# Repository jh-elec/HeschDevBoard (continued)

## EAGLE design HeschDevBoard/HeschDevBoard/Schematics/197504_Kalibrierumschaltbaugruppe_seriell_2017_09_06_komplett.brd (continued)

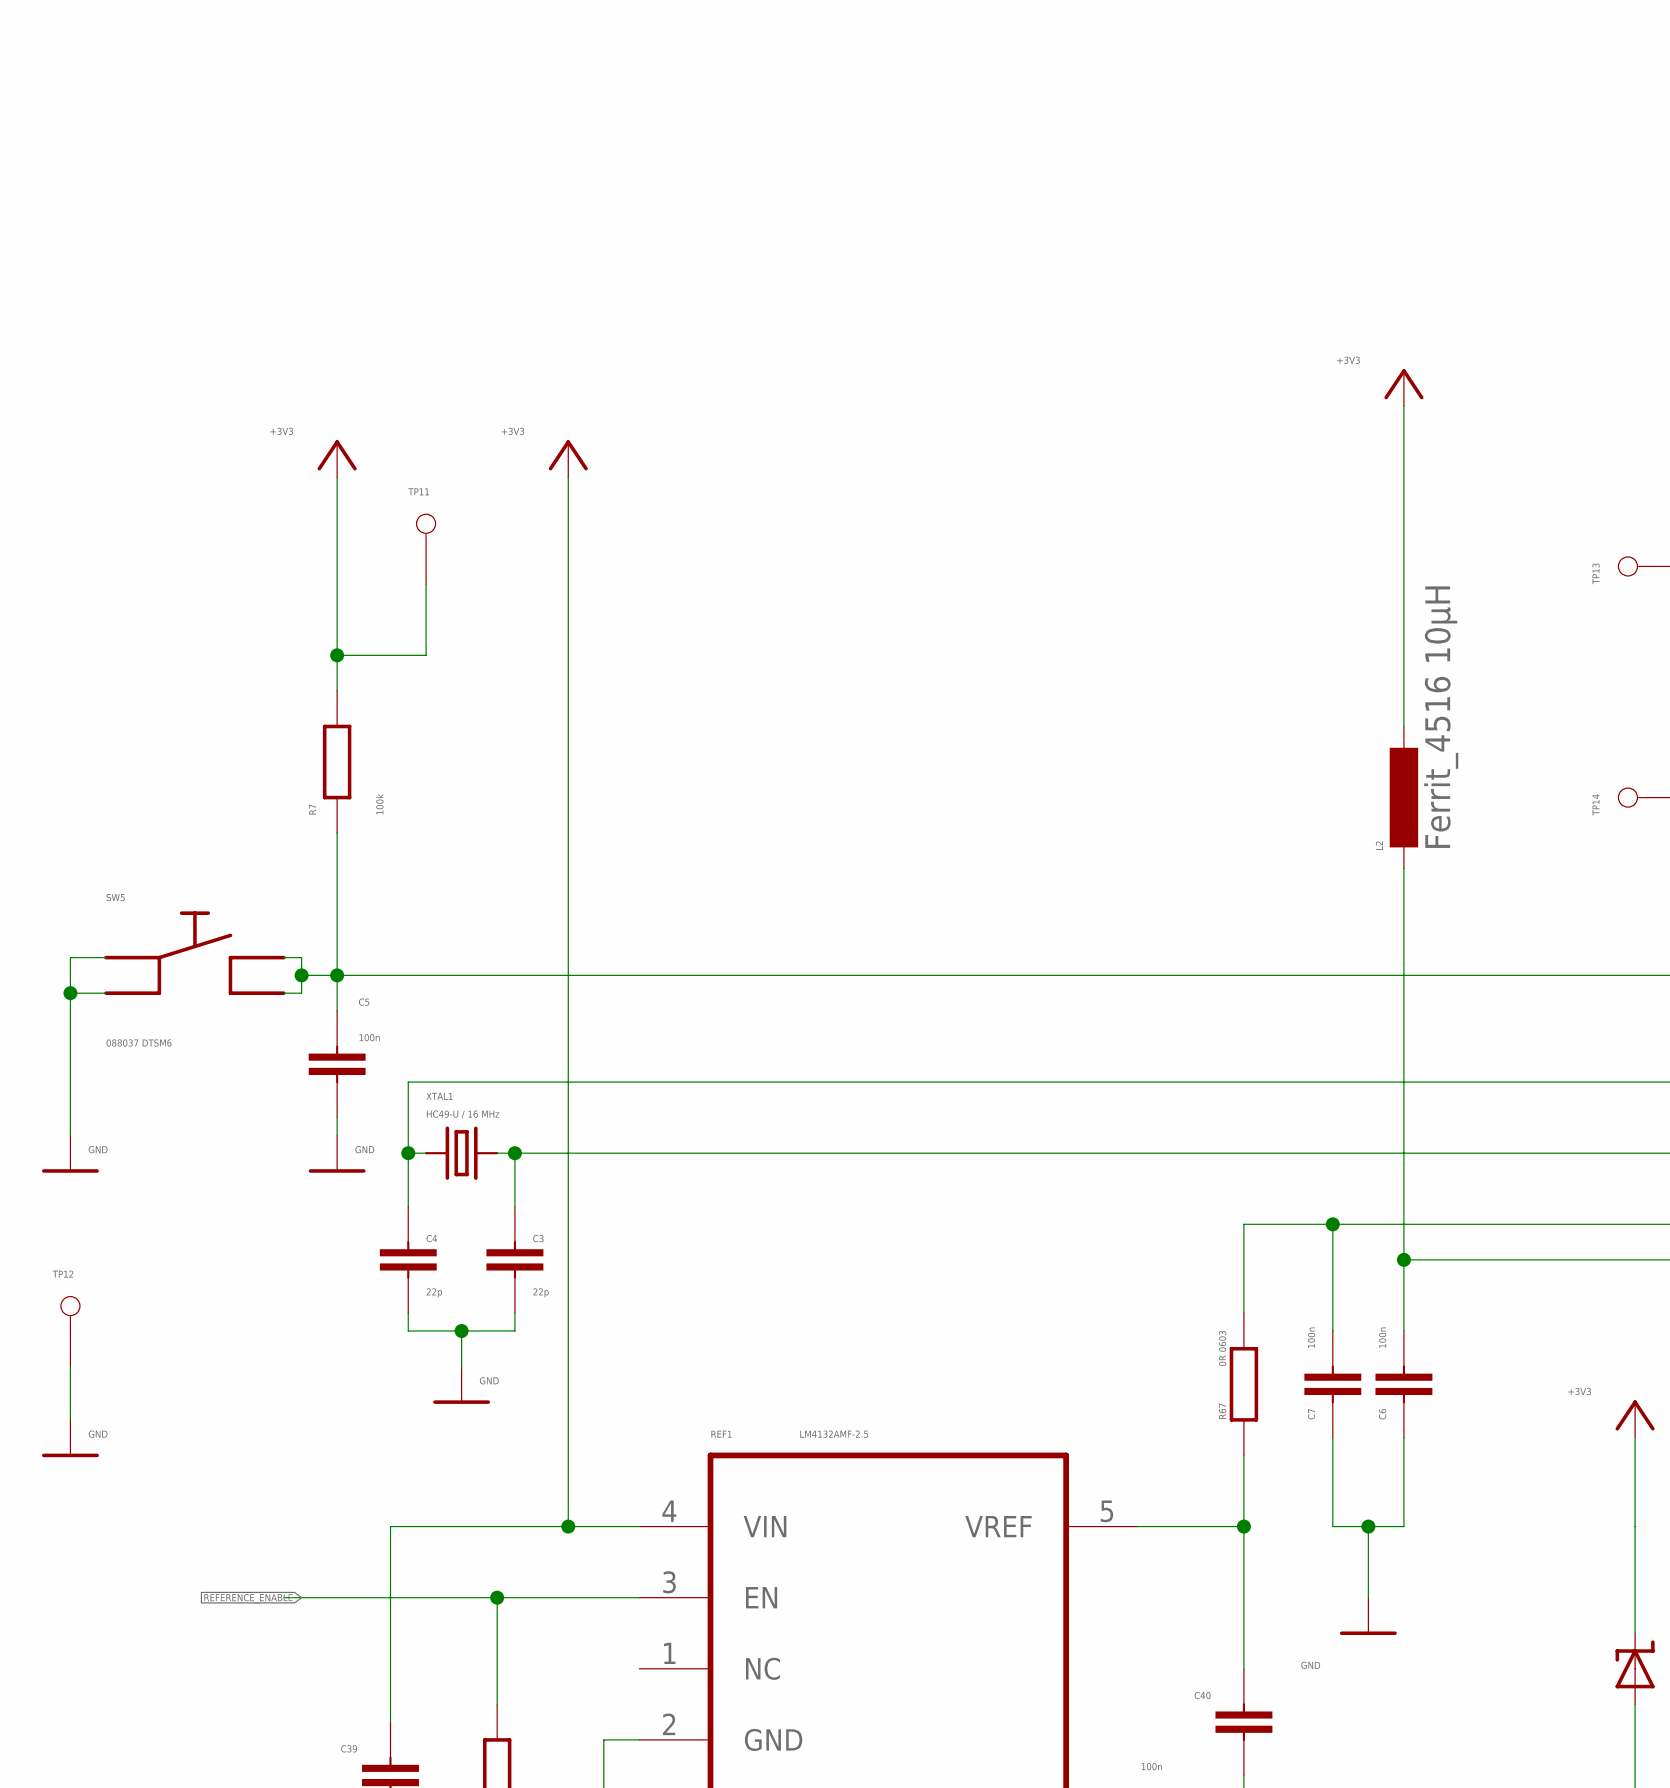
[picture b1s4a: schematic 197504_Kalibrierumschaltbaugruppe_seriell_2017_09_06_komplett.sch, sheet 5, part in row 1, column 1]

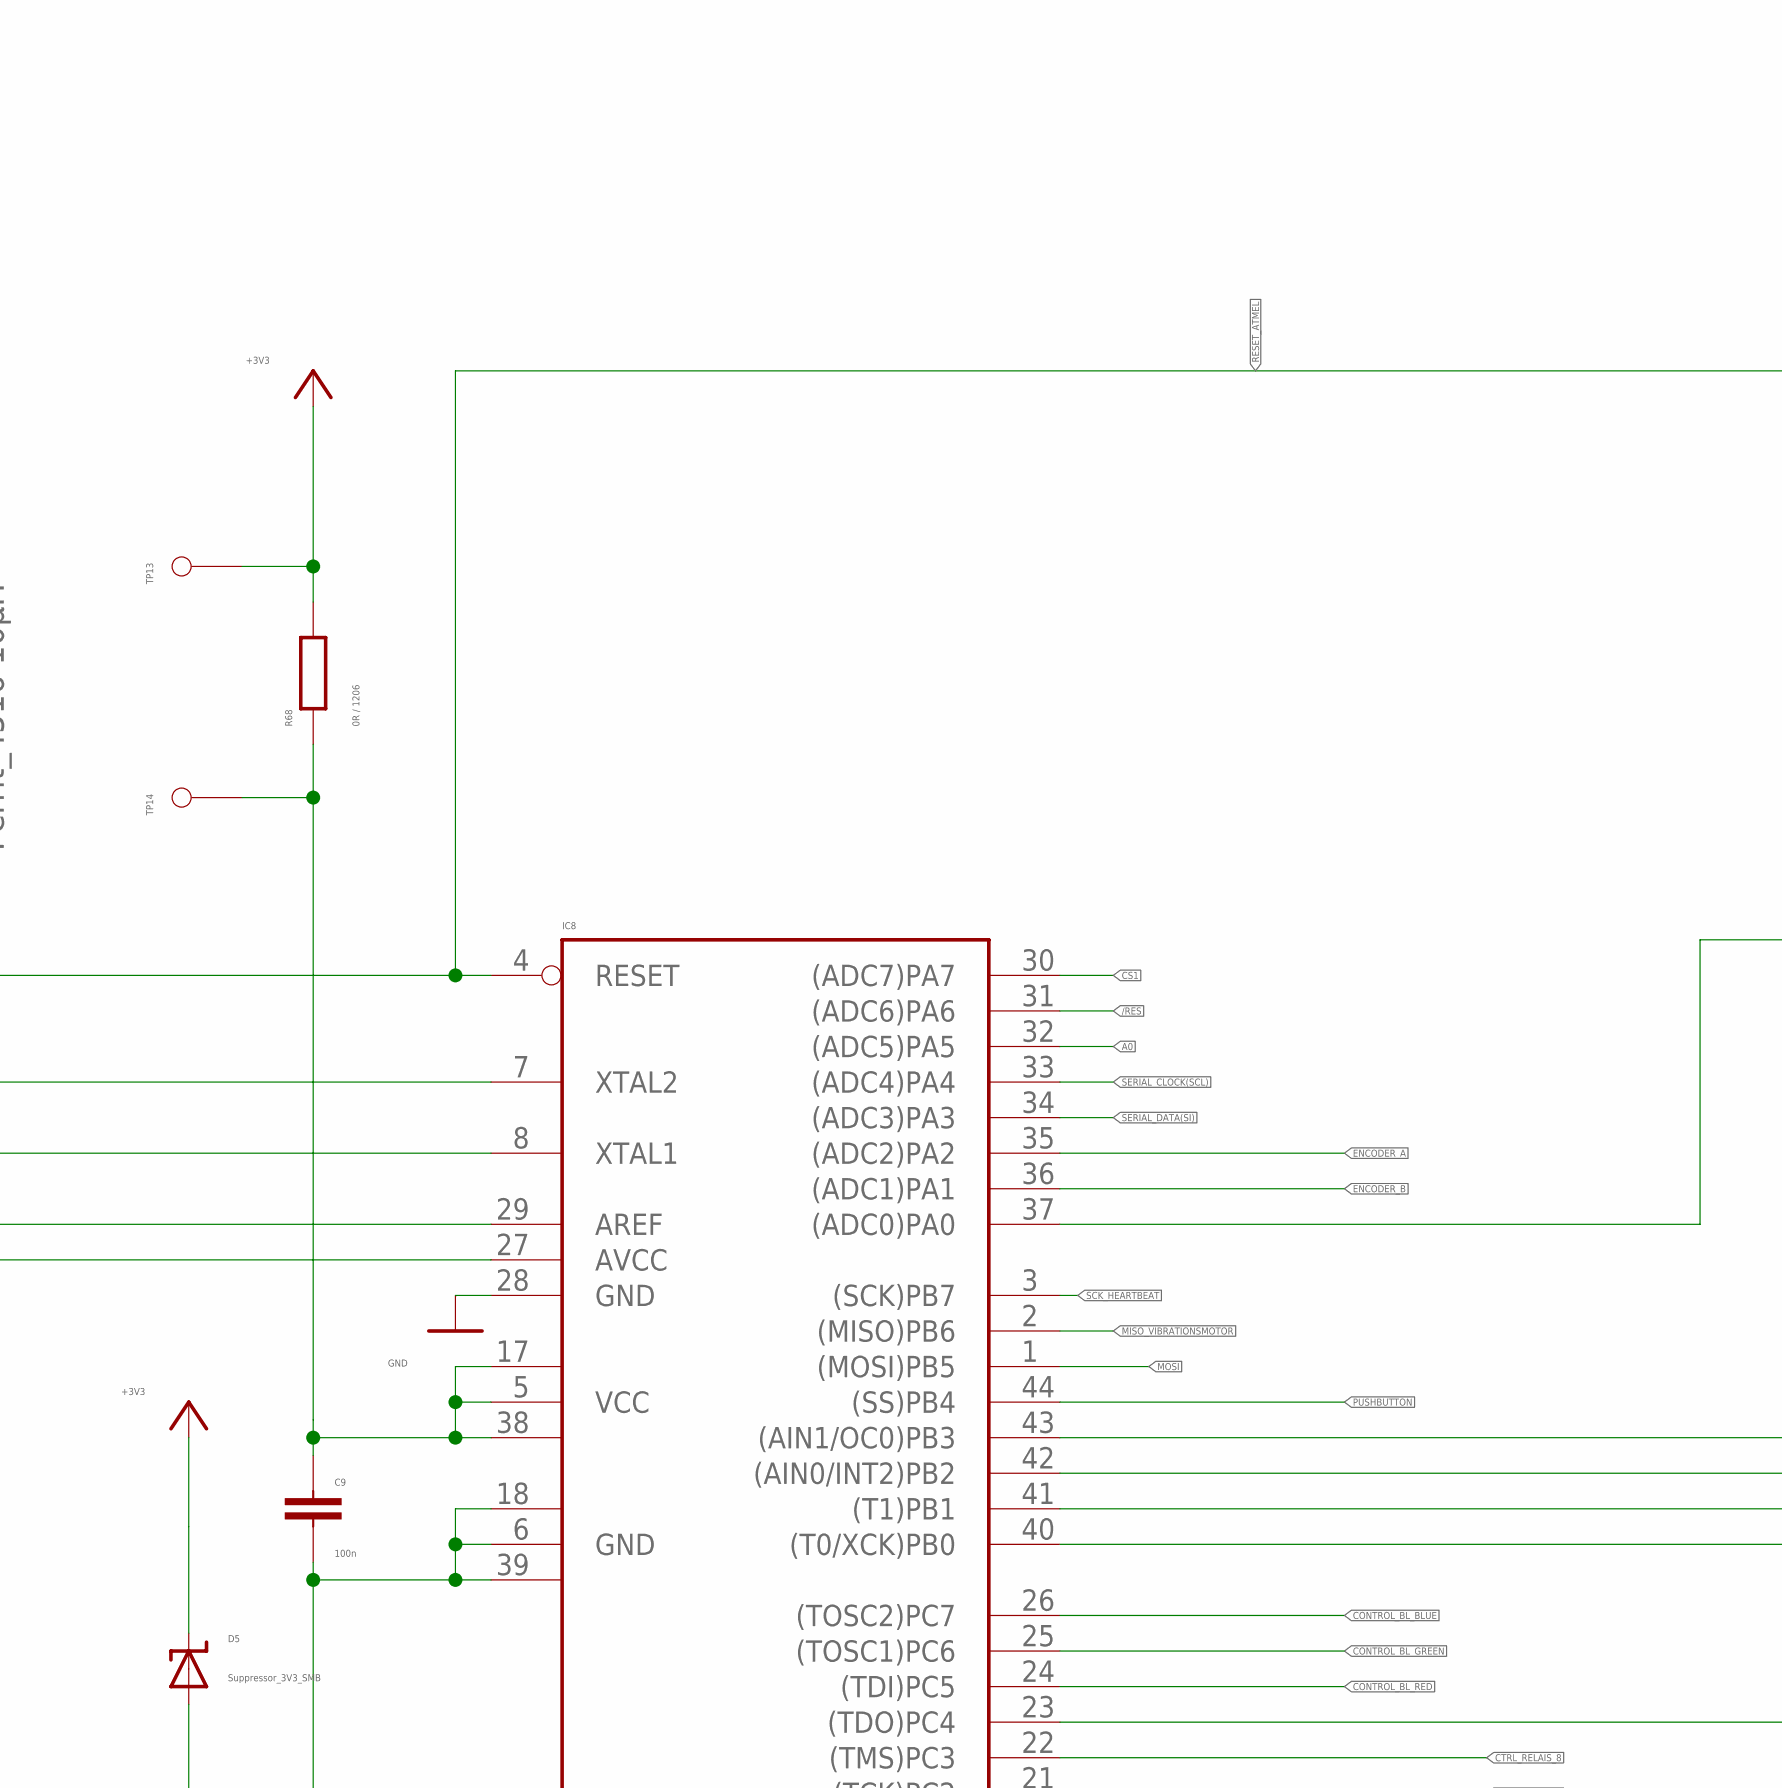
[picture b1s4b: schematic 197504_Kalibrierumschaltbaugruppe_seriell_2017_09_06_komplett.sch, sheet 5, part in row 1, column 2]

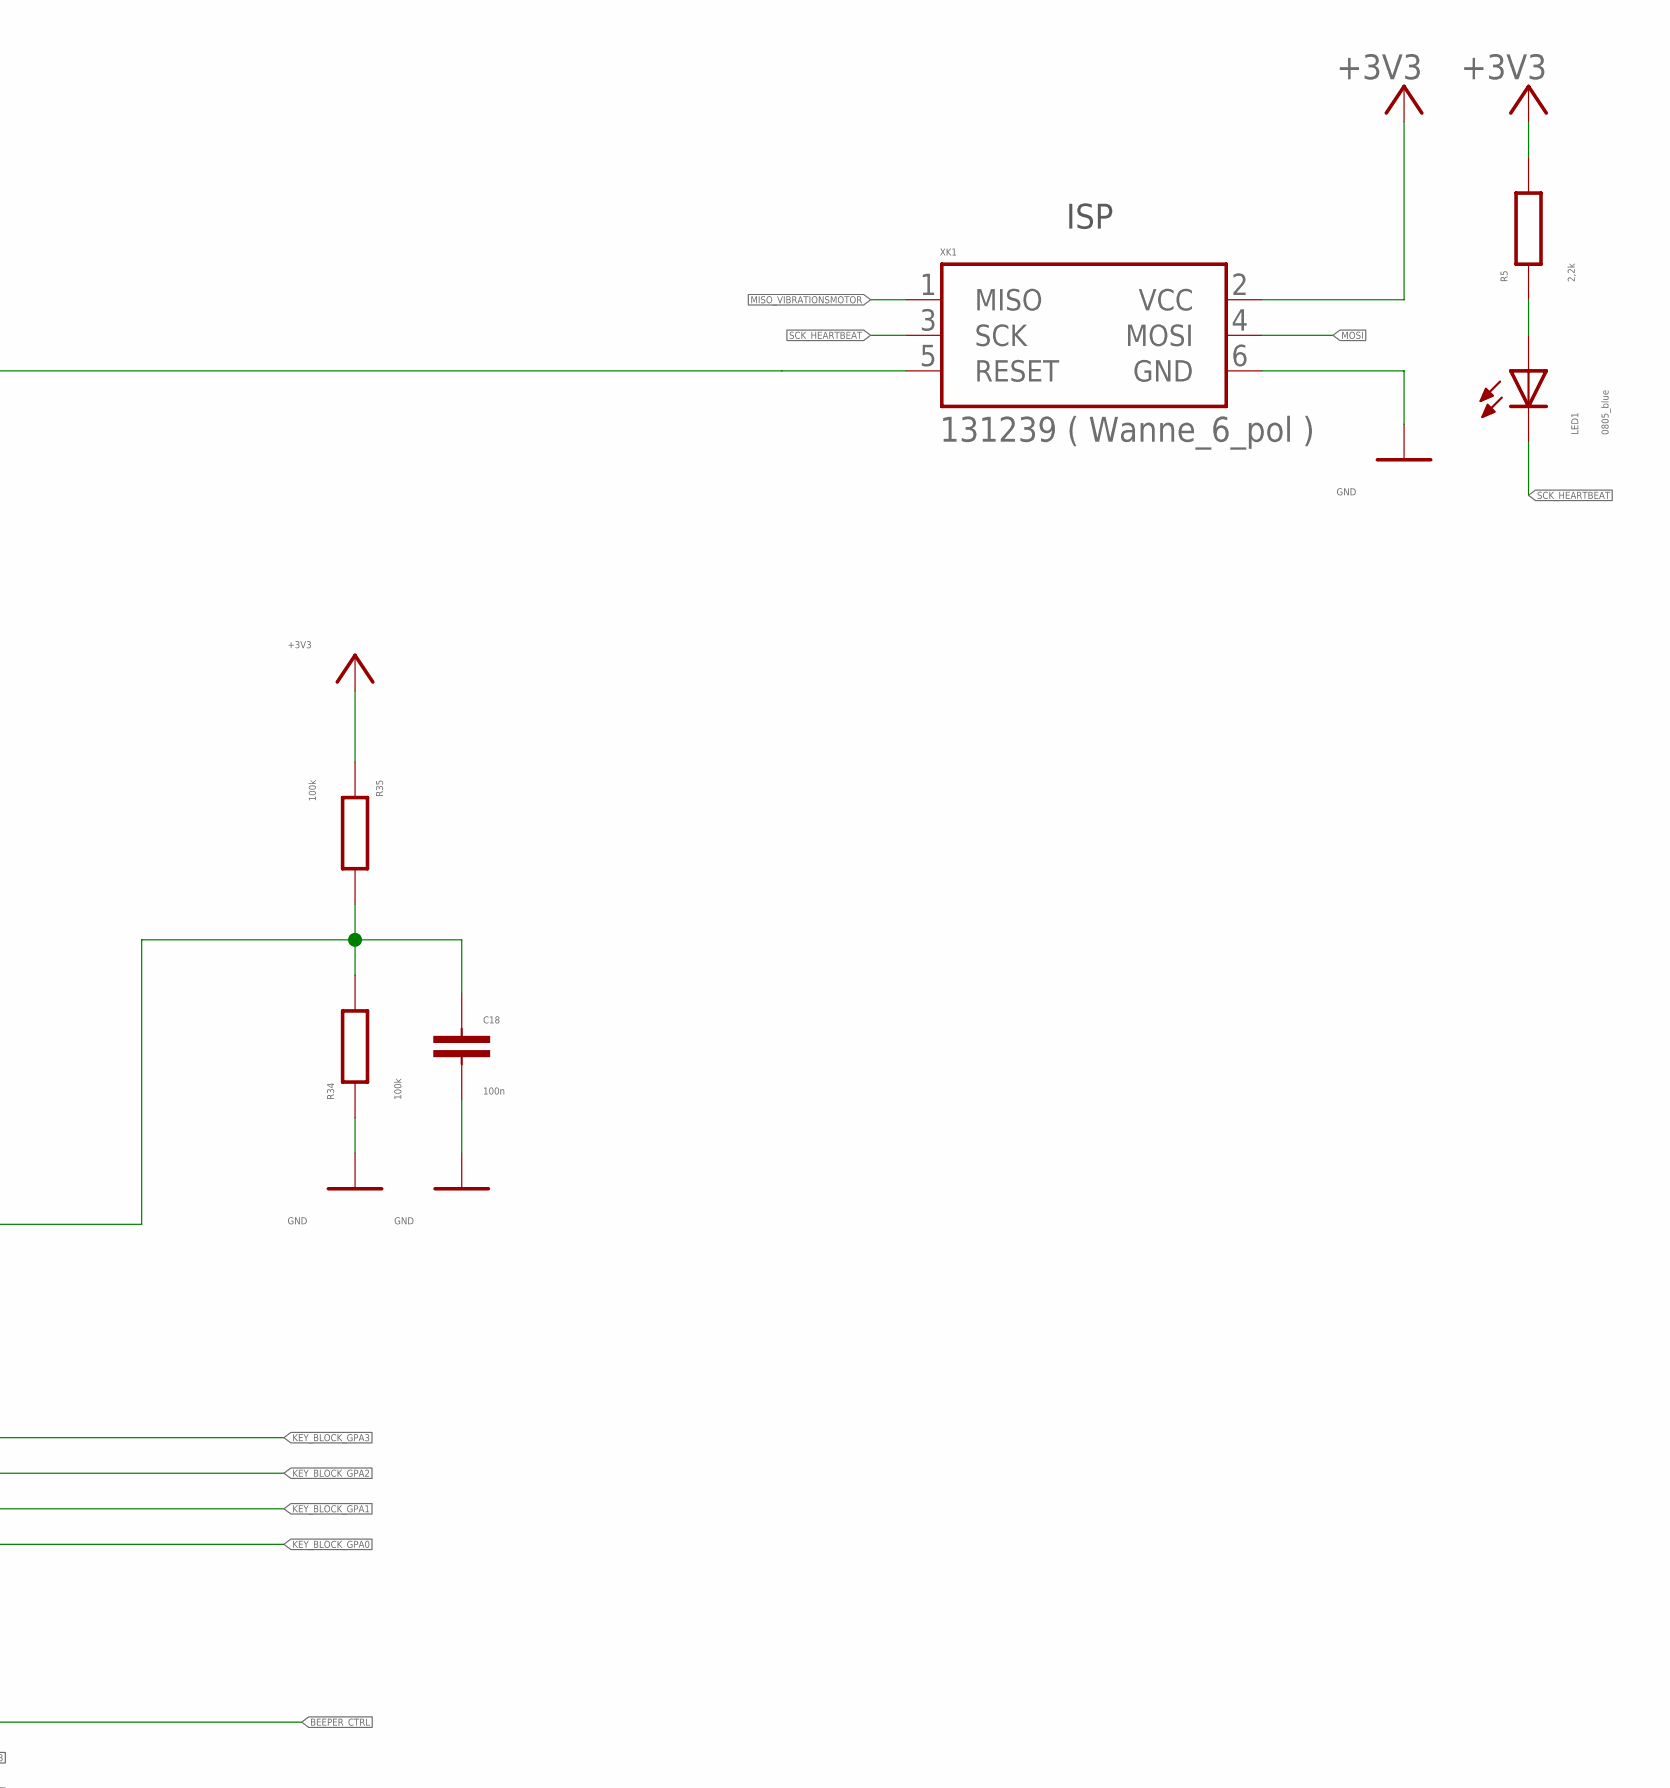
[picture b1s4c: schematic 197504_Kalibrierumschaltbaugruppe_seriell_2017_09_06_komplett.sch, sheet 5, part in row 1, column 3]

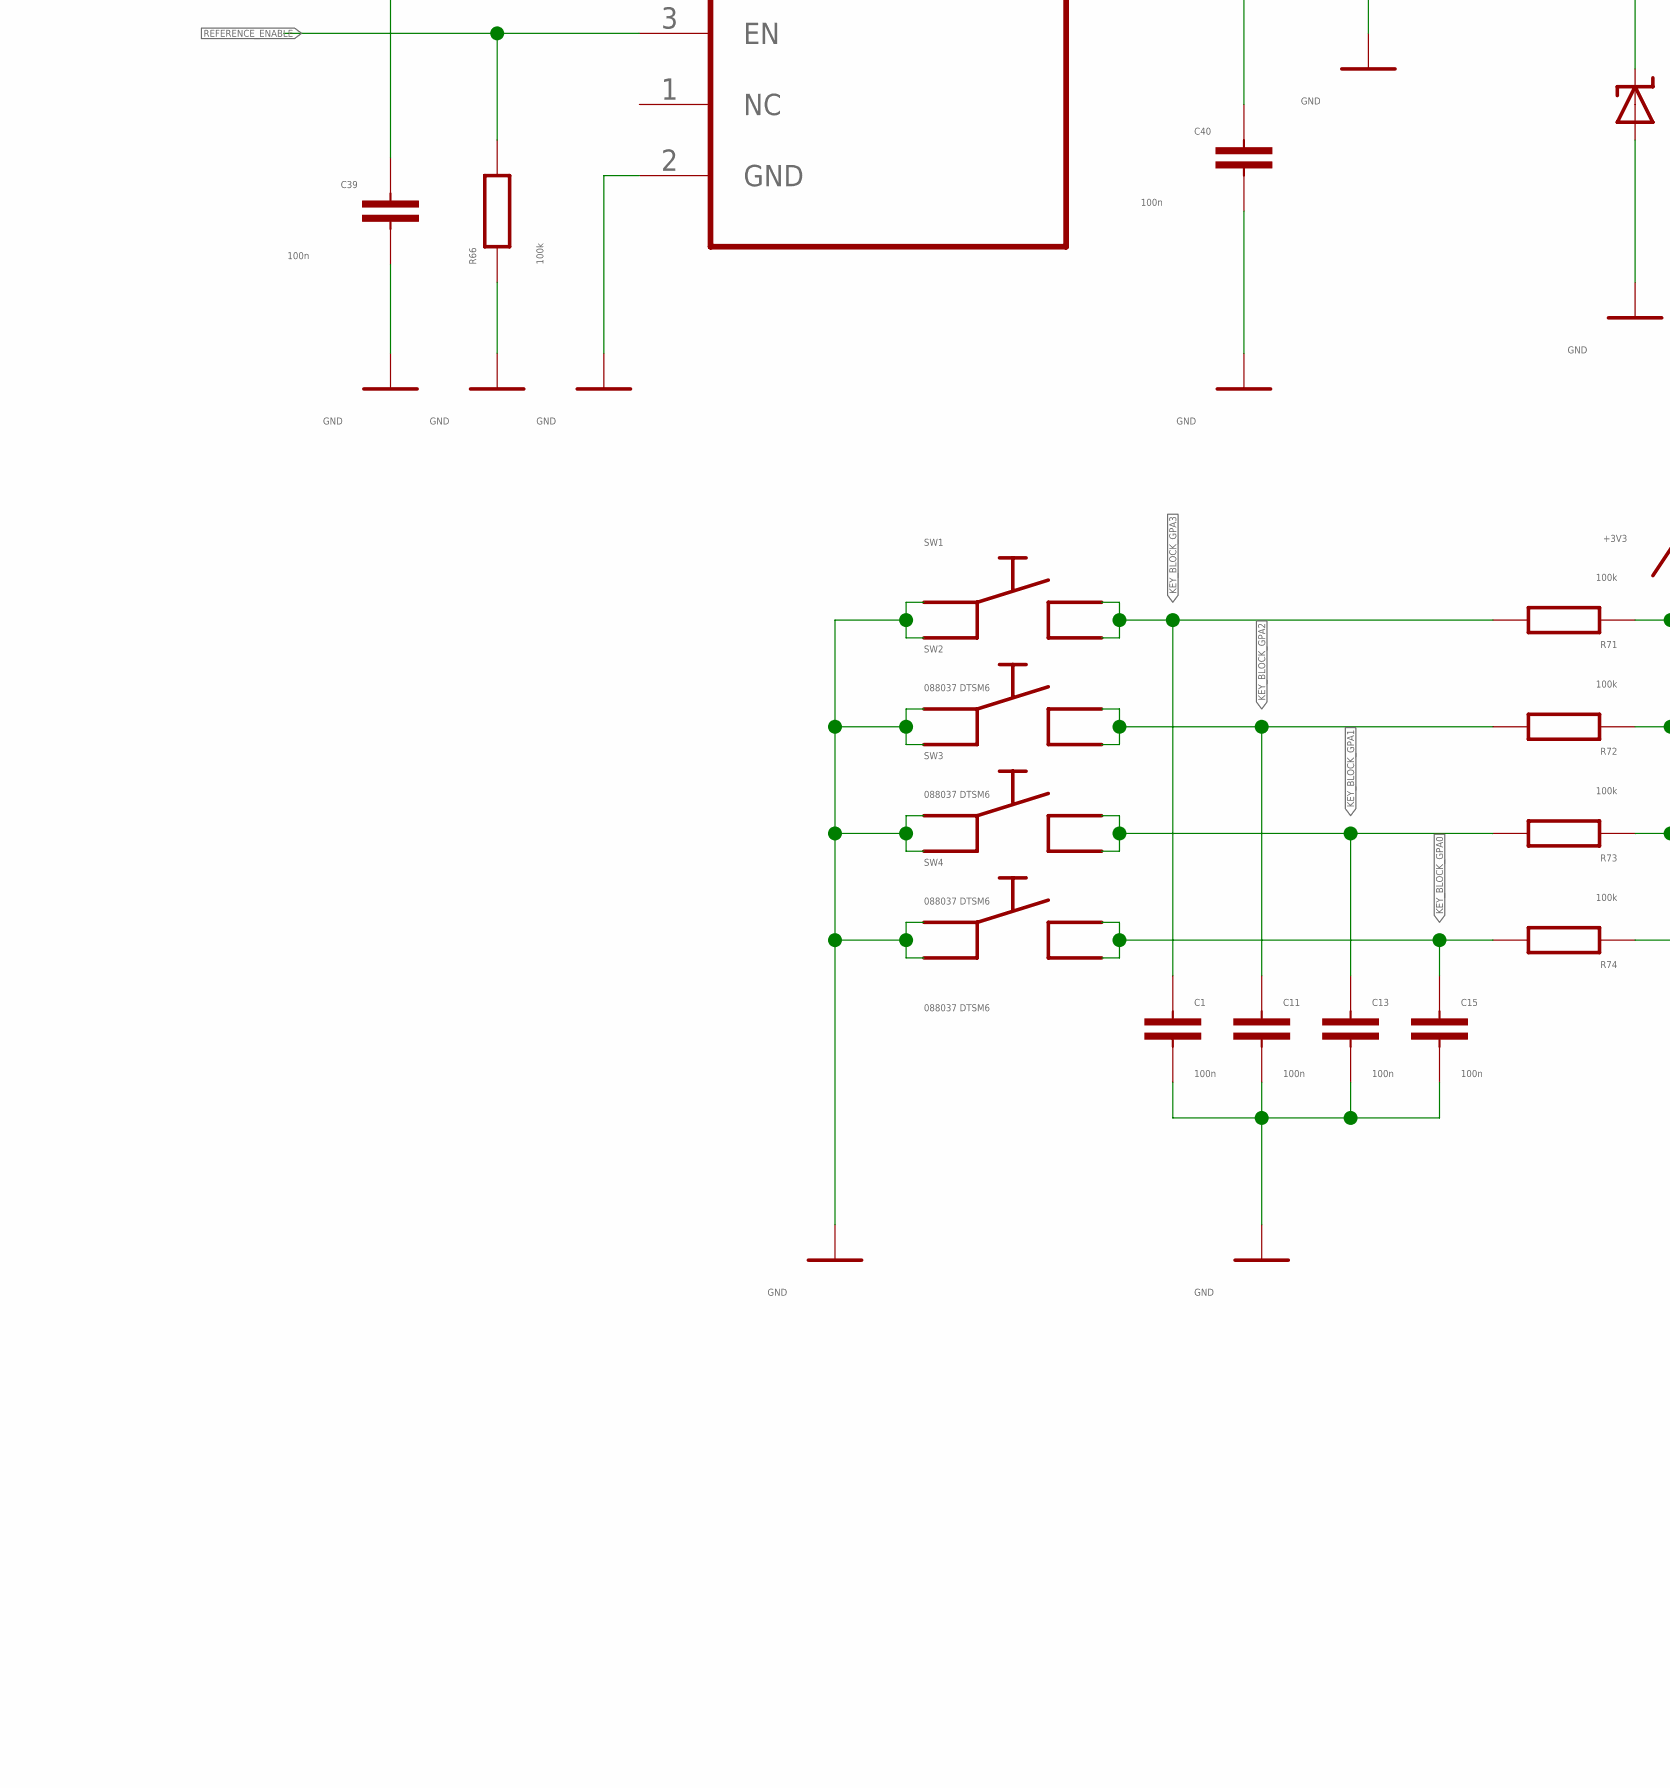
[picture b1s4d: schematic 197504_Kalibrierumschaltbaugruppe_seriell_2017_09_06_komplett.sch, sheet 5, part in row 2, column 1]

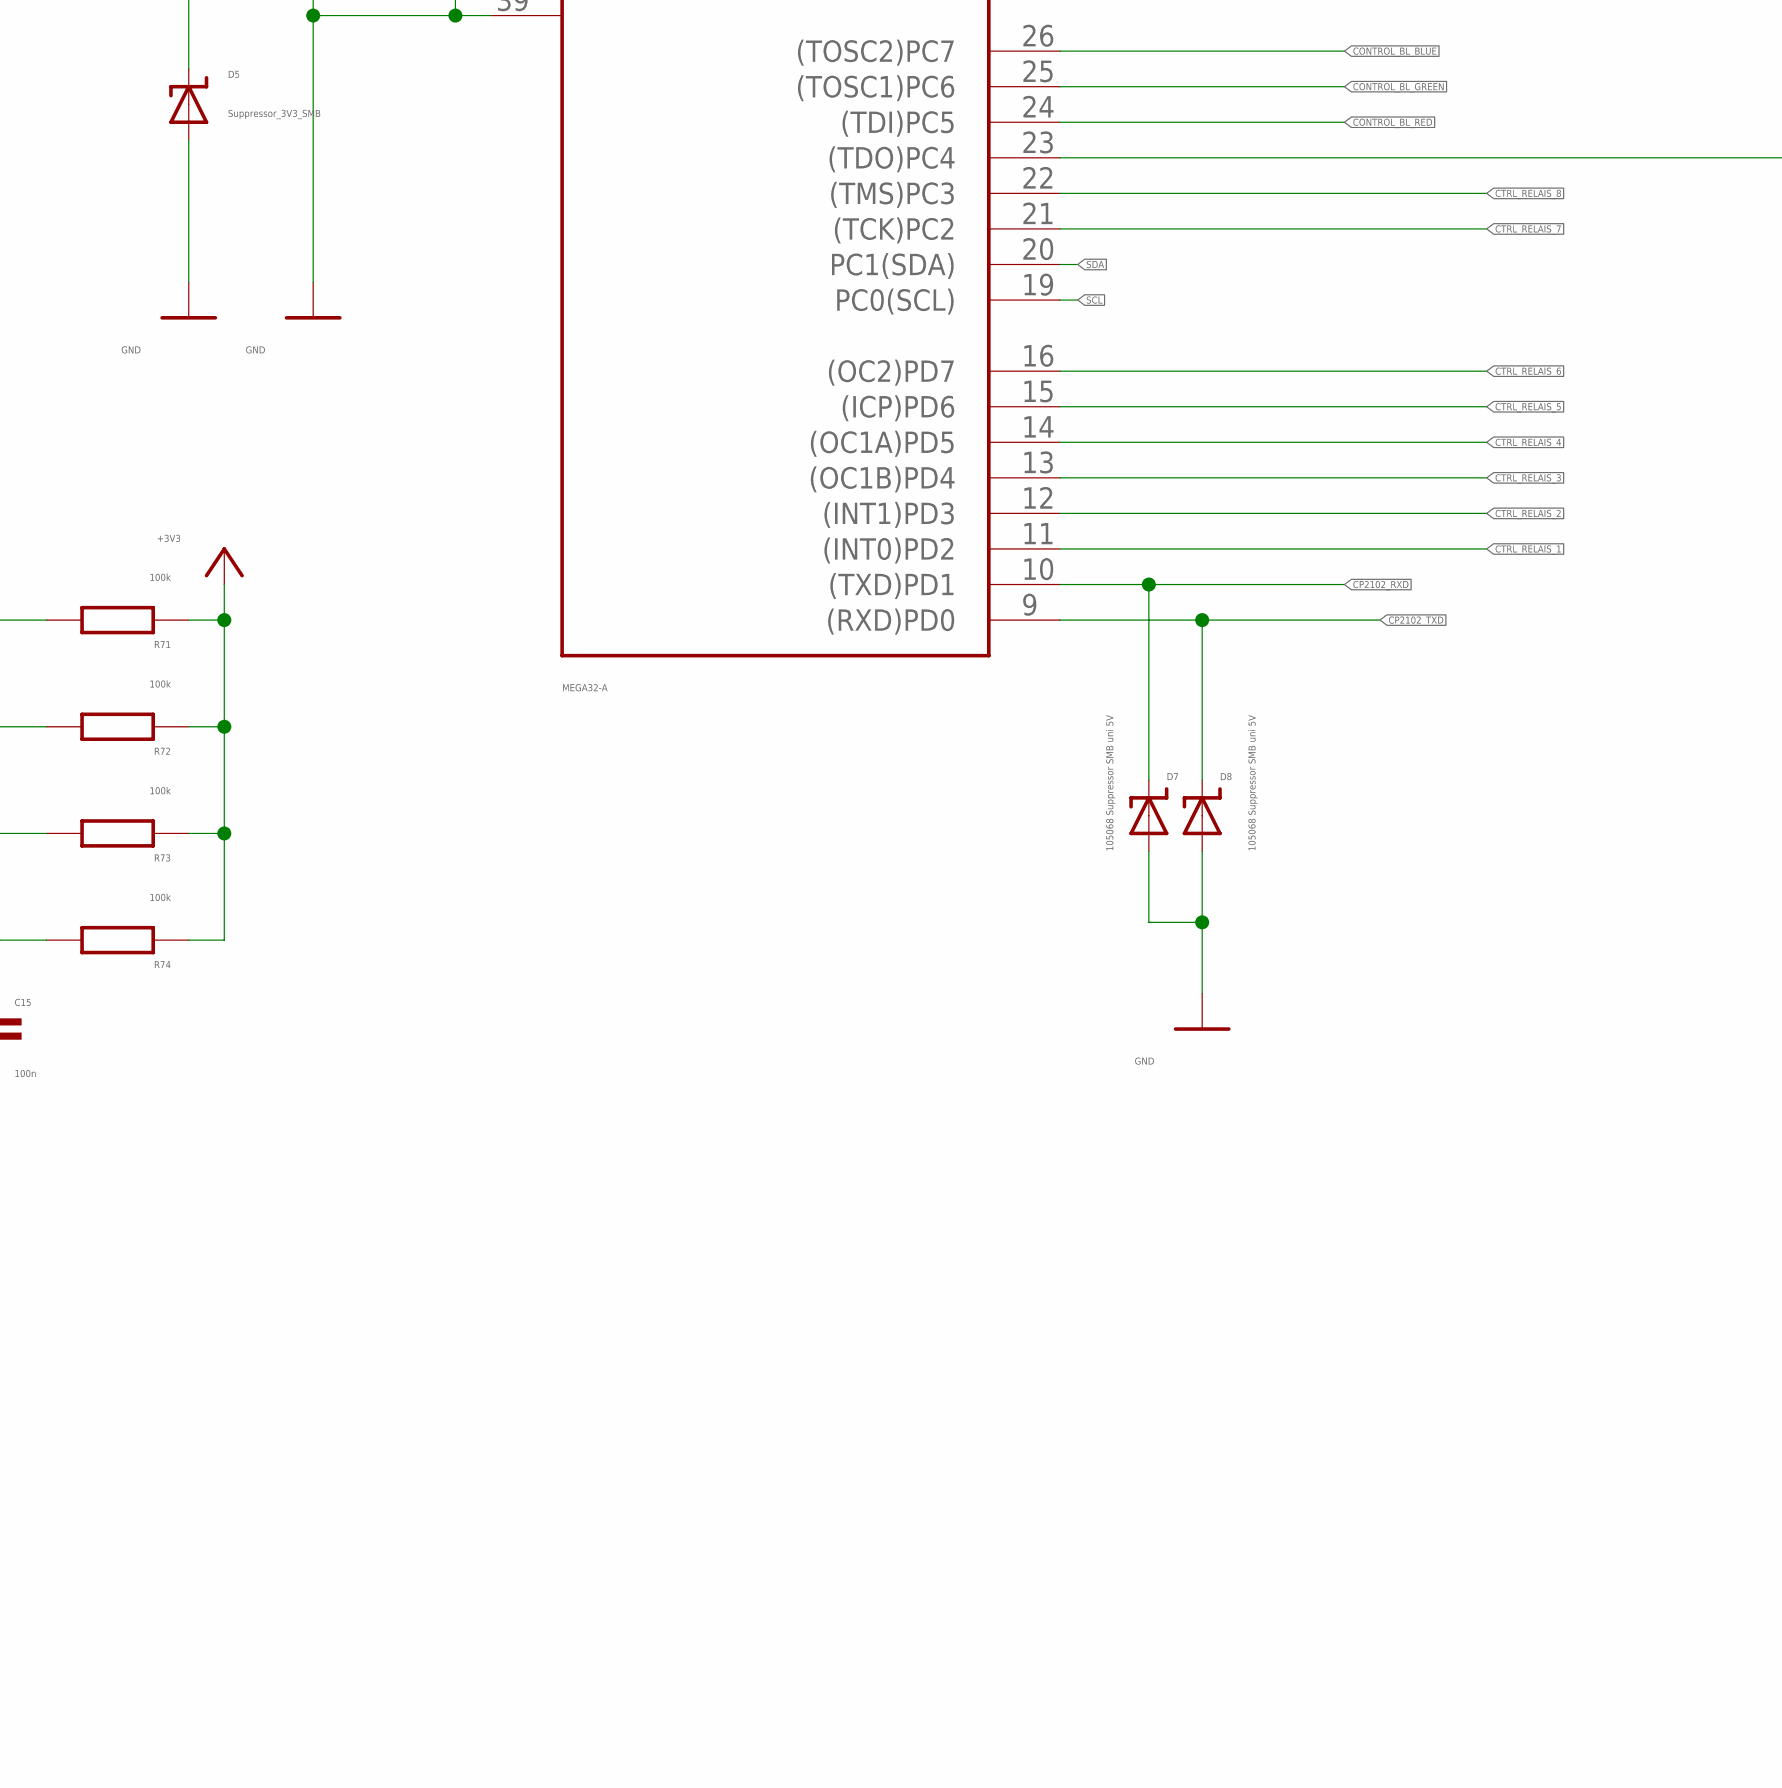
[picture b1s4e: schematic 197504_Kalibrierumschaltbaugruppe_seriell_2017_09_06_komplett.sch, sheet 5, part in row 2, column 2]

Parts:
C1, C5, C6, C7, C9, C11, C13, C15, C18, C39, C40: 100n; C0603
C3, C4: 22p; C0603
D5: Suppressor_3V3_SMB; SMBJ
D7, D8: 105068 Suppressor SMB uni 5V; SMBJ
IC8: MEGA32-A; TQFP44
L2: Ferrit_4516 10µH; L4516C
LED1: 0805_blue; CHIPLED_0805
R5: 2,2k; R0603
R7, R34, R35, R66, R71, R72, R73, R74: 100k; R0603
R67: 0R 0603; R0603
R68: 0R / 1206; R1206
REF1: LM4132AMF-2.5; SOT95P284X122-5N
SW1, SW2, SW3, SW4, SW5: 088037 DTSM6; DTSM6
TP11, TP12, TP13, TP14: Testpunkt_mit_Bohrung; THT-1X2,54
XK1: 131239 ( Wanne_6_pol ); WSL
XTAL1: HC49-U / 16 MHz; HC49

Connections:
+3V3: C39.1, D5.C, L2.1, R5.2, R7.2, R35.1, R68.2, R71.1, R72.1, R73.1, R74.1, REF1.4 (VIN), TP11.TP, TP13.TP, XK1.2 (VCC); also elsewhere on the board
/RES: IC8.31 ((ADC6)PA6); also elsewhere on the board
A0: IC8.32 ((ADC5)PA5); also elsewhere on the board
AREF: C7.1, IC8.29 (AREF), R67.2
AVCC: C6.1, IC8.27 (AVCC), L2.2
BEEPER_CTRL: IC8.23 ((TDO)PC4); also elsewhere on the board
CONTROL_BL_BLUE: IC8.26 ((TOSC2)PC7); also elsewhere on the board
CONTROL_BL_GREEN: IC8.25 ((TOSC1)PC6); also elsewhere on the board
CONTROL_BL_RED: IC8.24 ((TDI)PC5); also elsewhere on the board
CP2102_RXD: D7.C, IC8.10 ((TXD)PD1); also elsewhere on the board
CP2102_TXD: D8.C, IC8.9 ((RXD)PD0); also elsewhere on the board
CS1: IC8.30 ((ADC7)PA7); also elsewhere on the board
CTRL_RELAIS_1: IC8.11 ((INT0)PD2); also elsewhere on the board
CTRL_RELAIS_2: IC8.12 ((INT1)PD3); also elsewhere on the board
CTRL_RELAIS_3: IC8.13 ((OC1B)PD4); also elsewhere on the board
CTRL_RELAIS_4: IC8.14 ((OC1A)PD5); also elsewhere on the board
CTRL_RELAIS_5: IC8.15 ((ICP)PD6); also elsewhere on the board
CTRL_RELAIS_6: IC8.16 ((OC2)PD7); also elsewhere on the board
CTRL_RELAIS_7: IC8.21 ((TCK)PC2); also elsewhere on the board
CTRL_RELAIS_8: IC8.22 ((TMS)PC3); also elsewhere on the board
ENCODER_A: IC8.35 ((ADC2)PA2); also elsewhere on the board
ENCODER_B: IC8.36 ((ADC1)PA1); also elsewhere on the board
GND: C1.2, C3.2, C4.2, C5.2, C6.2, C7.2, C9.2, C11.2, C13.2, C15.2, C18.2, C39.2, C40.2, D5.A, D7.A, D8.A, IC8.6 (GND), IC8.18 (GND1), IC8.28 (GND), IC8.39 (GND2), R34.1, R66.1, REF1.2 (GND), SW1.1, SW1.2, SW2.1, SW2.2, SW3.1, SW3.2, SW4.1, SW4.2, SW5.1, SW5.2, TP12.TP, XK1.6 (GND); also elsewhere on the board
KEY_BLOCK_GPA0: C15.1, IC8.40 ((T0/XCK)PB0), R74.2, SW4.3, SW4.4
KEY_BLOCK_GPA1: C13.1, IC8.41 ((T1)PB1), R73.2, SW3.3, SW3.4
KEY_BLOCK_GPA2: C11.1, IC8.42 ((AIN0/INT2)PB2), R72.2, SW2.3, SW2.4
KEY_BLOCK_GPA3: C1.1, IC8.43 ((AIN1/OC0)PB3), R71.2, SW1.3, SW1.4
MESSGRößE_VERSORGUNGSSPANNUNG: C18.1, IC8.37 ((ADC0)PA0), R34.2, R35.2
MISO_VIBRATIONSMOTOR: IC8.2 ((MISO)PB6), XK1.1 (MISO); also elsewhere on the board
MOSI: IC8.1 ((MOSI)PB5), XK1.4 (MOSI)
unnamed: C9.1, IC8.5 (VCC), IC8.17 (VCC1), IC8.38 (VCC2), R68.1, TP14.TP
unnamed: LED1.A, R5.1
PUSHBUTTON: IC8.44 ((SS)PB4); also elsewhere on the board
REFERENCE_ENABLE: R66.2, REF1.3 (EN); also elsewhere on the board
RESET_ATMEL: C5.1, IC8.4 (RESET), R7.1, SW5.3, SW5.4, XK1.5 (RESET)
SCK_HEARTBEAT: IC8.3 ((SCK)PB7), LED1.C, XK1.3 (SCK)
SCL: IC8.19 (PC0(SCL)); also elsewhere on the board
SDA: IC8.20 (PC1(SDA)); also elsewhere on the board
SERIAL_CLOCK(SCL): IC8.33 ((ADC4)PA4); also elsewhere on the board
SERIAL_DATA(SI): IC8.34 ((ADC3)PA3); also elsewhere on the board
V_REF_OUT: C40.1, R67.1, REF1.5 (VREF)
XTAL1: C3.1, IC8.8 (XTAL1), XTAL1.1
XTAL2: C4.1, IC8.7 (XTAL2), XTAL1.2

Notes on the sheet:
Kalibrier- umschaltbaugruppe
ISP

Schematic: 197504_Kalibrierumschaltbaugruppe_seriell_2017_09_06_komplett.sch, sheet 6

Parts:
BUZ1: CA-M-SMD; SMD
D4: 105032 SS24; DO-214AA/SMB
IC1: LM317BD2T; D2PACK
IC3, IC4: ULN2003AD; SO16
K1, K2, K3, K4, K5, K6, K7, K8: # 035004 / TQ2SA-3V-Z TQ2SA-3V; PANASONIC_TQ_SMD
LED2, LED3, LED4, LED5, LED6, LED7, LED8, LED9, LED10, LED11: 0805_blue; CHIPLED_0805
R8, R15: 1k; R0603
R22, R23, R24, R25, R26, R27, R29, R30: 1k; R0805
R28, R62, R63, R64: 072083 47R; R2010
SJ1, SJ2: Lötjumper; SJ
VM1: LA4-436B
X1, X2, X3: MSTB 2,5/6-GF-5,08 AU ( Phoenix: 1949364 ); MSTB6_GF

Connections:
+3V3: BUZ1.4 (+), IC3.9 (CD+), IC4.9 (CD+), K1.1 (PLUS), K2.1 (PLUS), K3.1 (PLUS), K4.1 (PLUS), K5.1 (PLUS), K6.1 (PLUS), K7.1 (PLUS), K8.1 (PLUS), LED4.A, LED6.A, LED8.A, LED10.A, R8.1, R15.1, R23.2, R25.2, R27.2, R30.2, VM1.P$1 (+); also elsewhere on the board
AV_CHANNEL1: K6.4 (NO1), K6.7 (NO1), X2.3
AV_CHANNEL2: K5.4 (NO1), K5.7 (NO1), X2.4
AV_CHANNEL3: K8.4 (NO1), K8.7 (NO1), X3.3
AV_CHANNEL4: K7.4 (NO1), K7.7 (NO1), X3.4
BEEPER_BOOST: BUZ1.1 (-), IC4.12 (O5)
BEEPER_CTRL: IC4.5 (I5); also elsewhere on the board
CLK_OUT_LED: IC3.5 (I5); also elsewhere on the board
CLK_OUT_LED_: IC3.12 (O5), LED2.C
CTRL_RELAIS_1: IC3.2 (I2); also elsewhere on the board
CTRL_RELAIS_2: IC3.4 (I4); also elsewhere on the board
CTRL_RELAIS_3: IC4.1 (I1); also elsewhere on the board
CTRL_RELAIS_4: IC4.3 (I3); also elsewhere on the board
CTRL_RELAIS_5: IC3.1 (I1); also elsewhere on the board
CTRL_RELAIS_6: IC3.3 (I3); also elsewhere on the board
CTRL_RELAIS_7: IC4.2 (I2); also elsewhere on the board
CTRL_RELAIS_8: IC4.4 (I4); also elsewhere on the board
GND: IC3.8 (GND), IC4.8 (GND); also elsewhere on the board
KALIBRATOR+: K1.3 (COM1), K2.3 (COM1), K3.3 (COM1), K4.3 (COM1), X1.3
KALIBRATOR-: IC1.1 (ADJ), K1.8 (COM1), K2.8 (COM1), K3.8 (COM1), K4.8 (COM1), R28.1, R63.1, R64.1, X1.2, X1.4
KNOTEN_AV_VOLTAGES: D4.C, IC1.3 (IN), K5.3 (COM1), K5.8 (COM1), K6.3 (COM1), K6.8 (COM1), K7.3 (COM1), K7.8 (COM1), K8.3 (COM1), K8.8 (COM1), X1.1
MISO_VIBRATIONSMOTOR: IC4.6 (I6); also elsewhere on the board
unnamed: R63.2, SJ2.1
unnamed: LED4.C, R22.2
unnamed: R62.1, R64.2
unnamed: R62.2, SJ1.2
unnamed: LED5.A, R23.1
unnamed: LED6.C, R24.2
unnamed: LED7.A, R25.1
unnamed: LED8.C, R26.2
unnamed: LED9.A, R27.1
unnamed: D4.A, IC1.2 (OUT), R28.2, SJ1.1, SJ2.2
unnamed: LED10.C, R29.2
unnamed: LED11.A, R30.1
unnamed: LED3.A, R15.2
unnamed: LED2.A, R8.2
unnamed: K4.4 (NO1), X3.2
unnamed: K2.7 (NO1), X2.1
unnamed: K4.7 (NO1), X3.1
unnamed: K3.7 (NO1), X3.5
unnamed: K3.4 (NO1), X3.6
unnamed: K2.4 (NO1), X2.2
unnamed: K1.7 (NO1), X2.5
unnamed: K1.4 (NO1), X2.6
RELAIS_6_OUT: IC3.14 (O3), K6.10 (MINUS), R24.1
REL_1_OUT: IC3.15 (O2), K1.10 (MINUS), LED5.C
REL_2_OUT: IC3.13 (O4), K2.10 (MINUS), LED7.C
REL_3_OUT: IC4.16 (O1), K3.10 (MINUS), LED9.C
REL_4_OUT: IC4.14 (O3), K4.10 (MINUS), LED11.C
REL_5_OUT: IC3.16 (O1), K5.10 (MINUS), R22.1
REL_7_OUT: IC4.15 (O2), K7.10 (MINUS), R26.1
REL_8_OUT: IC4.13 (O4), K8.10 (MINUS), R29.1
RTC_INT_LED: IC3.6 (I6); also elsewhere on the board
RTC_INT_LED_: IC3.11 (O6), LED3.C
VIBRATIONSMOTOR_BOOST: IC4.11 (O6), VM1.P$2 (-)

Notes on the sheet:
Kalibrier- umschaltbaugruppe
AV4
AV3
AV2
AV1
